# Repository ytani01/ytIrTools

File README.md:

# ytIrTools for Raspberry Pi

Raspberry Pi + pigpio + python3 による、赤外線リモコン制御・解析ツール

## 概要

* LIRCなどは使わず、pigpioのPythonライブラリで作成 -- 高性能で高い柔軟性
* 正確な信号解析(IrAnalyze.py)
* 信号フォーマットは、AEHA,SONY,NEC以外に、DYSON,BOSEほか、あらゆる機器に対応
* 送受信を同時に行える
* 赤外線送受信につかうGPIOピンを(PWM用の12, 13, 18, 19以外で)自由に選べる

ちなみに…
GPIO の ON/OFF で信号を出しているのではなく、
pigpioの wave関数を使って、高品質な赤外線信号を作成してます。

## 注意

PWM用のピン(GPIO 12,13,18,19)は、使用しないで下さい。

* pigpiodをデフォルト(クロック=PCM)で立ち上げると不安定になる??

## インストール

### ytIrTools

```bash
# cd ~
$ python3 -m venv env-ir
$ cd env-ir
$ git clone https://www.github.com/ytani01/ytIrTools.git
$ cd ytIrTools
$ ./setup.sh
```

#### crontab の設定 (自動起動、自動再起動)
このとき、crontabの設定が上書きされます。
直前の設定内容は、``crontab.bak``に保存されます。
必要に応じて、``crontab -e``コマンドなどで、設定を調整して下さい。

```bash
$ crontab -l > crontab.bak
$ crontab crontab.sample
```

### Node-RED

Node-REDのインストール
```bash
bash < \(curl -sL https://raw.githubusercontent.com/node-red/linux-installers/master/deb/update-nodejs-and-nodered\)
```

追加フロー
* node-red-dashbaord
* alexa-home-skil

## ハードウェア

下記のページの回路を使うと、強力な赤外線信号を広範囲に送信できます。

* [IRRC32(IRServer32) - ESP32で赤外線学習リモコン](https://github.com/Goji2100/IRRC32)

## Comands

### [pigpiod](http://abyz.me.uk/rpi/pigpio/)

事前に pigpiod を起動する必要があります。
上記設定を行えば、自動的に起動するので、下記を行う必要はありません。

```bash
$ sudo pigpiod -t 0
```
* オプション「-t 0」がないと、不安定になる(?)

自動起動する場合は、crontabを設定。(crontab.sample 参照)

(注意) コマンドラインで "$ crontab crontab.sample" を実行すると、
今までの crontabが全て消去されます！

### ir-send (IrSendCmdClient.py) -- 赤外線信号コマンド

実体は、``IrSendCmdClient.py``です。
(python venvを``activate``してから、このスクリプトを呼び出します。)

デバイス名とボタン名を指定して、赤外線信号を送信する。
デバイス名・ボタンの設定は後述。

引数がない場合は、デバイス一覧、
デバイス名だけを指定した場合は、ボタン一覧
を表示。
```
$ ir-send -h

Usage: IrSendCmdClient.py [OPTIONS] [ARG]...

  IrSendCmdClient

Options:
  -s, --svrhost TEXT  server hostname
  -p, --port INTEGER  server port nubmer
  -d, --debug         debug flag
  -h, --help          Show this message and exit.

$ ir-send.py dev1 button1 button2
デバイス「dev1」のボタン「button1」と「button2」を連続して送信

$ ir-send.py
設定されているデバイス一覧

$ ir-send.py dev1
デバイス「dev1」に設定されているボタン一覧

$ ir-send.py @load
設定ファイルの再読み込み

```

### ir-analyze (IrAnalyze.py) -- 赤外線信号受信・解析

実体は、``IrAnalyze.py``です。
(python venvを``activate``してから、このスクリプトを呼び出します。)

赤外線信号を受信して解析結果を表示する。

詳細な解析結果情報を
/tmp/ir_dump.irconf
に保存(追記)する。
(このファイルは設定ファイルとして利用可)

最新の受信データ(補正しない生のパルス情報)を
/tmp/pulse_space.txt
に保存する。

```
Usage: IrAnalyze.py [OPTIONS] [PIN]

  IR signal analyzer
  
Options:
  -n INTEGER     number of signal to anlyze
  -v, --verbose  verbose mode
  -d, --debug    debug flag
  -h, --help     Show this message and exit.
```

## 設定ファイル(*.irconf)

* JSON形式で記述します。
* 一つのファイルに複数のデバイス設定を記述することができます。
* ``ir-analyze`` の出力(``/tmp/ir_dump.irconf``)を元に、
デバイス名、ボタン名などを設定できます。
* マクロ文字列を使えば、効率良く、わかりやすい記述が可能。

### ファイル名

* 拡張子は「.irconf」。これ以外のファイルは無視されます。

### 検索パス

下記のパスに存在する全ての``*.irconf''ファイルを読み込みます。

1. カレントディレクトリ
2. ${HOME}/.irconf.d
3. /etc/irconf.d

### 書式 -- JSON

下記の書式で、JSONフォーマット・ファイルを作成する。

* example 1
```
{
  "comment": "example 1",
  "header": {
    "dev_name": ["lamp", "ball_lamp"],
    "format":   "NEC",
    "T":        557.735294,
    "sym_tbl": {
      "-":      [[16, 8]],
      "=":      [],
      "0":      [[1, 1]],
      "1":      [[1, 3]],
      "/":      [[1, 71], [1, 73], [1, 108], [1, 1875]],
      "*":      [[16, 4]],
      "?":      []
    },
    "macro": {
      "[prefix]": "00F7",
      "[suffix]": "F /*/"
    }
  },
  "buttons": {
    "on":  ["- [prefix] C03 [suffix]", 2],
    "off": ["- [prefix] 40B [suffix]", 2]
  }
}
```

* example 2
```
{
  "comment": "example 2",
  "header": {
    "dev_name": ["sony_bl", "bl"],
    "format":   "SONY",
    "T":        598.750000,
    "sym_tbl": {
      "-":      [[4, 1]],
      "=":      [],
      "0":      [[1, 1]],
      "1":      [[2, 1]],
      "/":      [[2, 20], [2, 1966]],
      "*":      [],
      "?":      []
    },
    "macro": {
      "[prefix]": "-(0b)",
      "[suffix]": "0101 1010 0111/"
    }
  },
  "buttons": {
    "ch_01":   ["[prefix] 000 0000 [suffix]", 3],
    "ch_02":   ["[prefix] 100 0000 [suffix]", 3],
    "ch_03":   ["[prefix] 010 0000 [suffix]", 3],
    "ch_04":   ["[prefix] 110 0000 [suffix]", 3],
  }
}
```

## ポート番号

* 51001: IrSendCmdServer
* 51002: AutoAirconServer

## References

* [pigpio](http://abyz.me.uk/rpi/pigpio/)
* [IRRC32(IRServer32) - ESP32で赤外線学習リモコン](https://github.com/Goji2100/IRRC32)
* [irdb](http://irdb.tk/)
* [Codes for IR Remotes (for YTF IR Bridge)](https://github.com/arendst/Tasmota/wiki/Codes-for-IR-Remotes-(for-YTF-IR-Bridge))

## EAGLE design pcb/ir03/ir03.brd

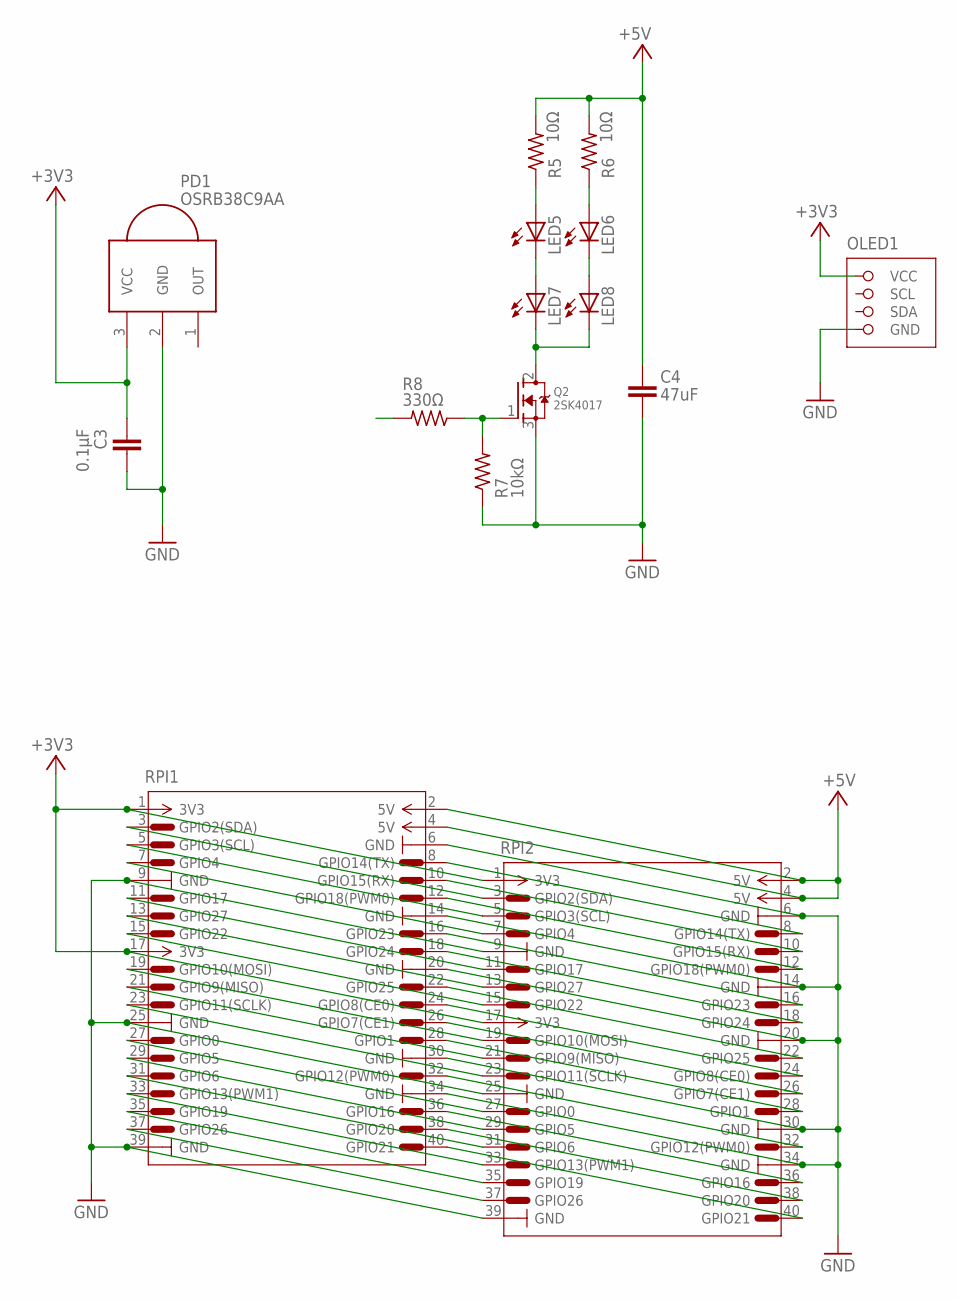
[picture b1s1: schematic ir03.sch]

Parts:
C3: 0.1μF; C025-025X050
C4: 47uF; C025-025X050
LED5, LED6, LED7, LED8: LED3MM
OLED1: OLED-SSD1306-0.96; OLED-I2C-0.96
PD1: OSRB38C9AA; PNA460XM
Q2: 2SK4017; TO220V
R5, R6: 10Ω; 0204/5
R7: 10kΩ; 0204/5
R8: 330Ω; 0204/5
RPI1, RPI2: RPI-PIN

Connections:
+3V3: C3.1, OLED1.VCC, PD1.3 (VCC), RPI1.1 (3V3), RPI1.17 (3V3), RPI2.1 (3V3), RPI2.17 (3V3)
+5V: C4.1, R5.2, R6.2, RPI1.2 (5V), RPI1.4 (5V), RPI2.2 (5V), RPI2.4 (5V)
GND: C3.2, C4.2, OLED1.GND, PD1.2 (GND), Q2.3 (S), R7.1, RPI1.6 (GND), RPI1.9 (GND), RPI1.14 (GND), RPI1.20 (GND), RPI1.25 (GND), RPI1.30 (GND), RPI1.34 (GND), RPI1.39 (GND), RPI2.6 (GND), RPI2.9 (GND), RPI2.14 (GND), RPI2.20 (GND), RPI2.25 (GND), RPI2.30 (GND), RPI2.34 (GND), RPI2.39 (GND)
unnamed: LED5.A, R5.1
unnamed: RPI1.3 (GPIO2(SDA)), RPI2.3 (GPIO2(SDA))
unnamed: RPI1.5 (GPIO3(SCL)), RPI2.5 (GPIO3(SCL))
unnamed: RPI1.7 (GPIO4), RPI2.7 (GPIO4)
unnamed: LED6.A, R6.1
unnamed: RPI1.11 (GPIO17), RPI2.11 (GPIO17)
unnamed: RPI1.13 (GPIO27), RPI2.13 (GPIO27)
unnamed: RPI1.15 (GPIO22), RPI2.15 (GPIO22)
unnamed: RPI1.23 (GPIO11(SCLK)), RPI2.23 (GPIO11(SCLK))
unnamed: RPI1.19 (GPIO10(MOSI)), RPI2.19 (GPIO10(MOSI))
unnamed: RPI1.21 (GPIO9(MISO)), RPI2.21 (GPIO9(MISO))
unnamed: LED5.K (C), LED7.A
unnamed: LED6.K (C), LED8.A
unnamed: LED7.K (C), LED8.K (C), Q2.2 (D)
unnamed: RPI1.8 (GPIO14(TX)), RPI2.8 (GPIO14(TX))
unnamed: RPI1.10 (GPIO15(RX)), RPI2.10 (GPIO15(RX))
unnamed: RPI1.12 (GPIO18(PWM0)), RPI2.12 (GPIO18(PWM0))
unnamed: RPI1.16 (GPIO23), RPI2.16 (GPIO23)
unnamed: RPI1.18 (GPIO24), RPI2.18 (GPIO24)
unnamed: RPI1.22 (GPIO25), RPI2.22 (GPIO25)
unnamed: Q2.1 (G), R7.2, R8.1
unnamed: RPI1.24 (GPIO8(CE0)), RPI2.24 (GPIO8(CE0))
unnamed: RPI1.26 (GPIO7(CE1)), RPI2.26 (GPIO7(CE1))
unnamed: RPI1.27 (GPIO0), RPI2.27 (GPIO0)
unnamed: RPI1.28 (GPIO1), RPI2.28 (GPIO1)
unnamed: RPI1.29 (GPIO5), RPI2.29 (GPIO5)
unnamed: RPI1.31 (GPIO6), RPI2.31 (GPIO6)
unnamed: RPI1.32 (GPIO12(PWM0)), RPI2.32 (GPIO12(PWM0))
unnamed: RPI1.33 (GPIO13(PWM1)), RPI2.33 (GPIO13(PWM1))
unnamed: RPI1.35 (GPIO19), RPI2.35 (GPIO19)
unnamed: RPI1.36 (GPIO16), RPI2.36 (GPIO16)
unnamed: RPI1.37 (GPIO26), RPI2.37 (GPIO26)
unnamed: RPI1.38 (GPIO20), RPI2.38 (GPIO20)
unnamed: RPI1.40 (GPIO21), RPI2.40 (GPIO21)

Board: 2 copper layers, 15 parts (0 on the bottom side), 37 nets, no tracks yet.

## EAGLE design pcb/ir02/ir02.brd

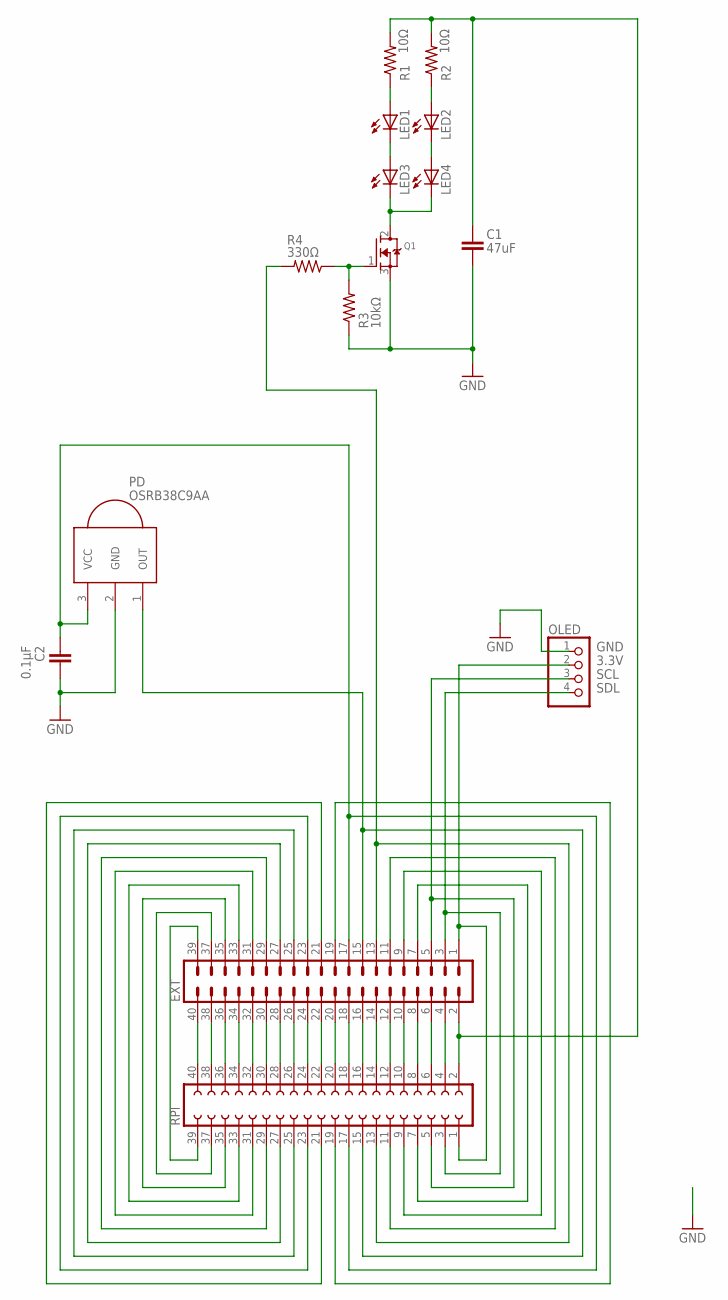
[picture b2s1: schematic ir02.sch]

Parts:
C1: 47uF; C025-025X050
C2: 0.1μF; C025-025X050
EXT: MA20-2
LED1, LED2, LED3, LED4: LED3MM
OLED: PINHD-1X4; 1X04
PD: OSRB38C9AA; PNA460XM
Q1: MOSFET-NGDS_TO220V; TO220V
R1, R2: 10Ω; 0204/5
R3: 10kΩ; 0204/5
R4: 330Ω; 0204/5
RPI: FE20-2

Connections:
3.3V: C2.1, EXT.1, EXT.17, OLED.2, PD.3 (VCC), RPI.1, RPI.17
5V: C1.1, EXT.2, R1.2, R2.2, RPI.2
GND: C1.2, C2.2, EXT.6, EXT.9, EXT.14, EXT.34, EXT.39, OLED.1, PD.2 (GND), Q1.3 (S), R3.1, RPI.6, RPI.9, RPI.14, RPI.34, RPI.39
unnamed: Q1.1 (G), R3.2, R4.1
unnamed: LED1.A, R1.1
unnamed: LED2.A, R2.1
unnamed: EXT.15, PD.1 (OUT), RPI.15
unnamed: LED1.K (C), LED3.A
unnamed: LED2.K (C), LED4.A
unnamed: LED3.K (C), LED4.K (C), Q1.2 (D)
unnamed: EXT.4, RPI.4
unnamed: EXT.8, RPI.8
unnamed: EXT.10, RPI.10
unnamed: EXT.12, RPI.12
unnamed: EXT.16, RPI.16
unnamed: EXT.18, RPI.18
unnamed: EXT.20, RPI.20
unnamed: EXT.22, RPI.22
unnamed: EXT.24, RPI.24
unnamed: EXT.26, RPI.26
unnamed: EXT.28, RPI.28
unnamed: EXT.30, RPI.30
unnamed: EXT.32, RPI.32
unnamed: EXT.36, RPI.36
unnamed: EXT.38, RPI.38
unnamed: EXT.40, RPI.40
unnamed: EXT.7, RPI.7
unnamed: EXT.11, RPI.11
unnamed: EXT.13, R4.2, RPI.13
unnamed: EXT.37, RPI.37
unnamed: EXT.35, RPI.35
unnamed: EXT.33, RPI.33
unnamed: EXT.31, RPI.31
unnamed: EXT.29, RPI.29
unnamed: EXT.27, RPI.27
unnamed: EXT.25, RPI.25
unnamed: EXT.23, RPI.23
unnamed: EXT.21, RPI.21
unnamed: EXT.19, RPI.19
SCL: EXT.5, OLED.3, RPI.5
SDL: EXT.3, OLED.4, RPI.3

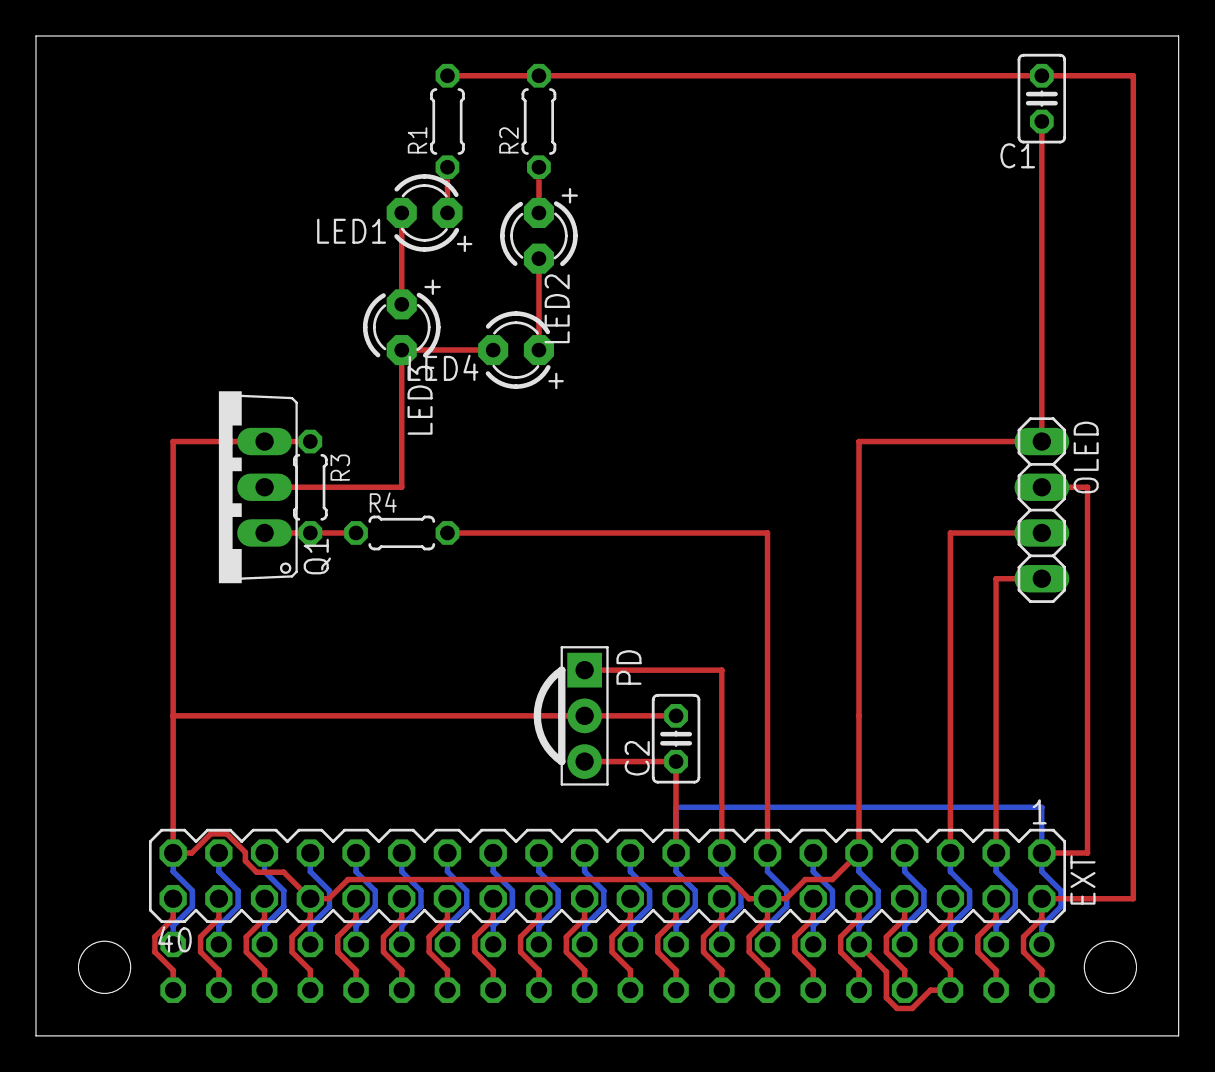
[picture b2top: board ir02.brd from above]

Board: 2 copper layers, 63.5 x 55.5 mm, 15 parts (1 on the bottom side), 41 nets.

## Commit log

2020-01-06 Set theme jekyll-theme-cayman
2020-02-19 node-red flow
2020-03-04 IrWsServer.py
2020-03-13 MM-BLEBC2
2021-02-01 [update] flow
2021-09-09 Add: irconf.d/small_lamp.irconf
2021-09-09 UPD: irconf.d
2021-09-10 UPD: rename boot.sh to boot-ir.sh
2021-09-29 UPD: pcb
2022-09-25 UPD: AutoAirconServer.py
2022-09-25 UPD: flow
2023-06-30 UPD: AutoAirconSever.py: mqtt.ytani.net: T.B.D.
2023-07-20 UPD: AutoAirconSever.py: -2 <= ki_i + kd_d <= 2
2024-07-29 UPD:
2025-07-26 ADD: uv/
2025-08-01 UPD: RTEMP_MIN = 18
